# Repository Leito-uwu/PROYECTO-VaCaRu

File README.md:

**PROTOTIPO DE SISTEMA DE CLASIFICACIÓN DE BOTELLAS DE VIDRIO AUTOMATIZADO POR COLOR**

**📝 Descripción del Proyecto**

Bienvenido a nuestro sistema de clasificación de botellas automatizado. Este proyecto está diseñado para optimizar y agilizar el proceso de separación de botellas según sus características, para esto estamos utilizando tecnología de electronica, mecánica y automatización.

Con este sistema, buscamos mejorar la eficiencia en la gestión de residuos, reducir costos operativos y promover prácticas más sostenibles en el reciclaje de envases. Nuestra solución integra sensores, procesamiento de diferenciacion de colores y algoritmos de clasificación para lograr una identificación rápida y precisa de los materiales.

¡Explora el repositorio y conoce más sobre cómo funciona este innovador sistema!

**🎯 Características Principales**

- 🔍 Clasificación Inteligente: Utiliza un sensor para identificar las caracteristicas de la botella.
- ⚡ Automatización Total: El sistema funciona de manera autónoma, reduciendo la necesidad de intervención humana.
- 🔄 Eficiencia en Procesamiento: Alta velocidad de detección y clasificación para optimizar la gestión de residuos.
- 🤖 Integración con Sensores: Emplea sensores para detectar el material y color de la botella
- 🌱 Enfoque en Sostenibilidad: Contribuye a la mejora del reciclaje y la reducción del impacto ambiental.
- 🛠️ Flexibilidad y Escalabilidad: Puede adaptarse a diferentes entornos y tipos de botellas.

**⚙️ Instalación y Configuración**

Reconfirgurable y programable, en el sentido que se puede tener acceso al codigo por ser un prototipo, y tomando en cuenta su configuracion de los sensores y actuadores. 

**🚀 Cómo Usarlo**
    Guía sobre la Funcionalidad:
    1) Colocar la botella en el comienzo de la cinta transportadora.
    2) Mediante el tablero de control, iniciar el proceso por la botonera.
    3) Detección del sensor de color e infrarrojo.
    4) Una vez detectado el brazo procede a la sujetación de la botella segun su color.
    5) Clasifica la botella en su respectivo deposito.
**🔎 Tecnologías Utilizadas**
ACTUADORES: 1 Mator Paso a Paso
            5 Servomotores
            1 Sensor FC-51
            1 Sensor TCS3200
            1 Pantalla LCD con I2C
            2 Pulsadores
            1 Driver ULN2003    
**👥 Contribución**
Autores: Alberto Ruiz
         Ramiro Caucota
         Leonardo Vargas

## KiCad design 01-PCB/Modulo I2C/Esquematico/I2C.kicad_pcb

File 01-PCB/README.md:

**PCB 👨‍💻**

Este apartado incluye los archivos necesarios para la fabricación y ensamblaje de la PCB del proyecto, como diseños en formato Gerber, esquemáticos, lista de materiales, archivos CAD y guías de ensamblaje de PCBs. Su objetivo es proporcionar toda la documentación requerida para replicar, modificar o mejorar el diseño original, asegurando una correcta integración del hardware con el sistema.

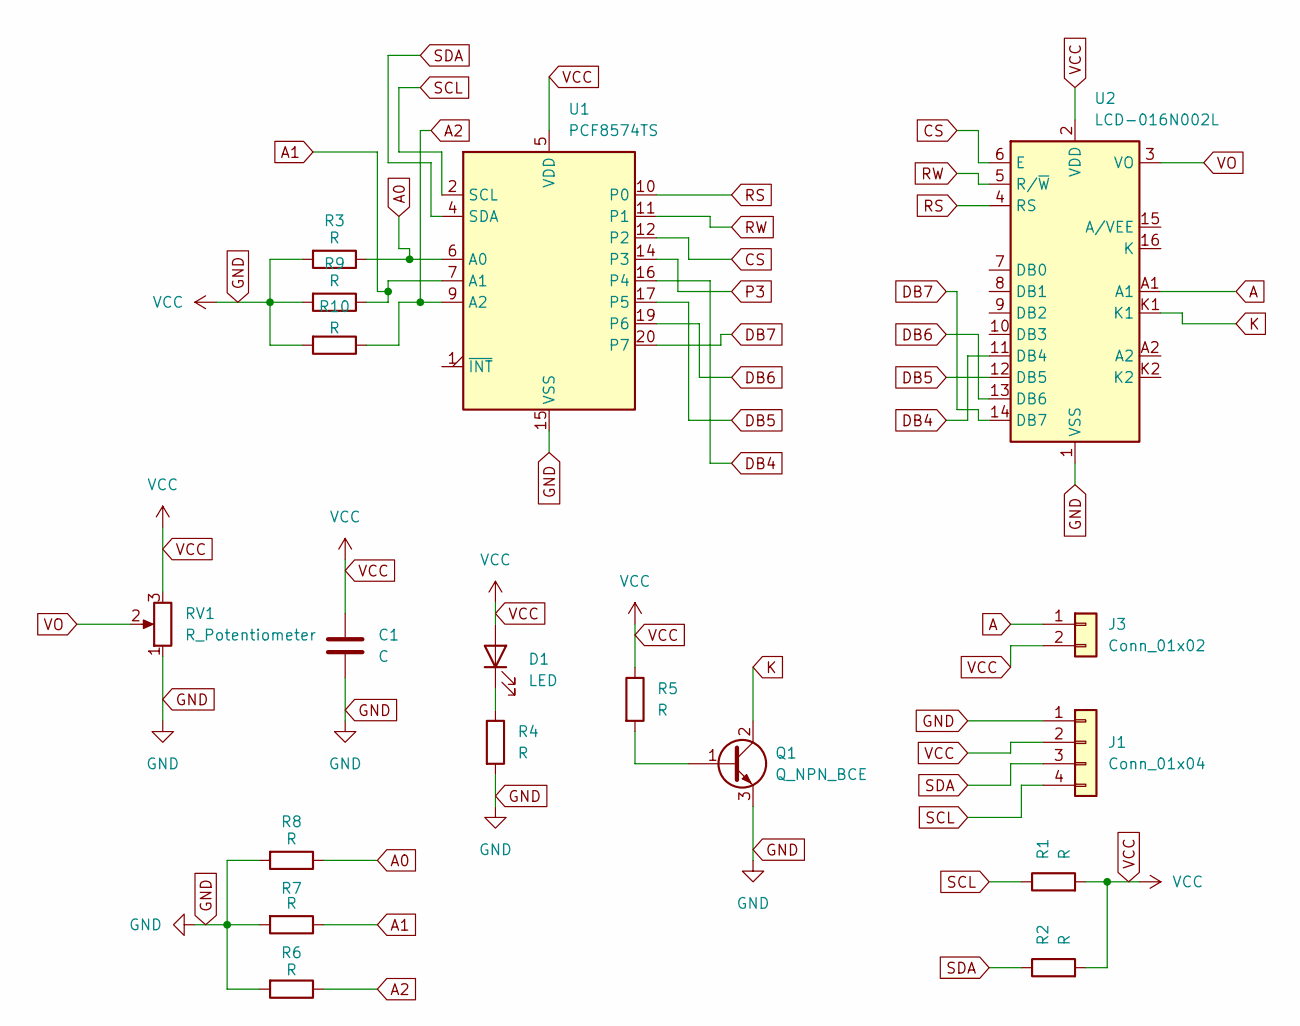
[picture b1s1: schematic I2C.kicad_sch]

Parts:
C1: C; C_0402_1005Metric
D1: LED; LED_D5.0mm_Horizontal_O1.27mm_Z3.0mm
J1: Conn_01x04; PhoenixContact_GMSTBA_2,5_4-G-7,62_1x04_P7.62mm_Horizontal
J3: Conn_01x02; PhoenixContact_GMSTBA_2,5_2-G_1x02_P7.50mm_Horizontal
Q1: Q_NPN_BCE; TO-92
R1, R2, R3, R4, R5, R6, R7, R8, R9, R10: R; R_0402_1005Metric
RV1: R_Potentiometer; Potentiometer_Bourns_3339H_Vertical
U1: PCF8574TS; SSOP-20_4.4x6.5mm_P0.65mm
U2: LCD-016N002L

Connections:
A: J3.1, U2.A1
A0: R3.1, R8.1, U1.6 (A0)
A1: R7.1, R9.1, U1.7 (A1)
A2: R6.1, R10.1, U1.9 (A2)
CS: U1.12 (P2), U2.6 (E)
DB4: U1.16 (P4), U2.11 (DB4)
DB5: U1.17 (P5), U2.12 (DB5)
DB6: U1.19 (P6), U2.13 (DB6)
DB7: U1.20 (P7), U2.14 (DB7)
GND: C1.1, C1.2, D1.2 (A), J1.1, J1.2, J3.2, Q1.3 (E), R1.2, R2.2, R3.2, R4.2, R5.1, R6.2, R7.2, R8.2, R9.2, R10.2, RV1.1, RV1.3, U1.5 (VDD), U1.15 (VSS), U2.1 (VSS), U2.2 (VDD)
K: Q1.2 (C), U2.K1
unnamed: D1.1 (K), R4.1
unnamed: Q1.1 (B), R5.2
P3: U1.14 (P3)
RS: U1.10 (P0), U2.4 (RS)
RW: U1.11 (P1), U2.5 (R/~W)
SCL: J1.4, R1.1, U1.2 (SCL)
SDA: J1.3, R2.1, U1.4 (SDA)
VO: RV1.2, U2.3 (VO)

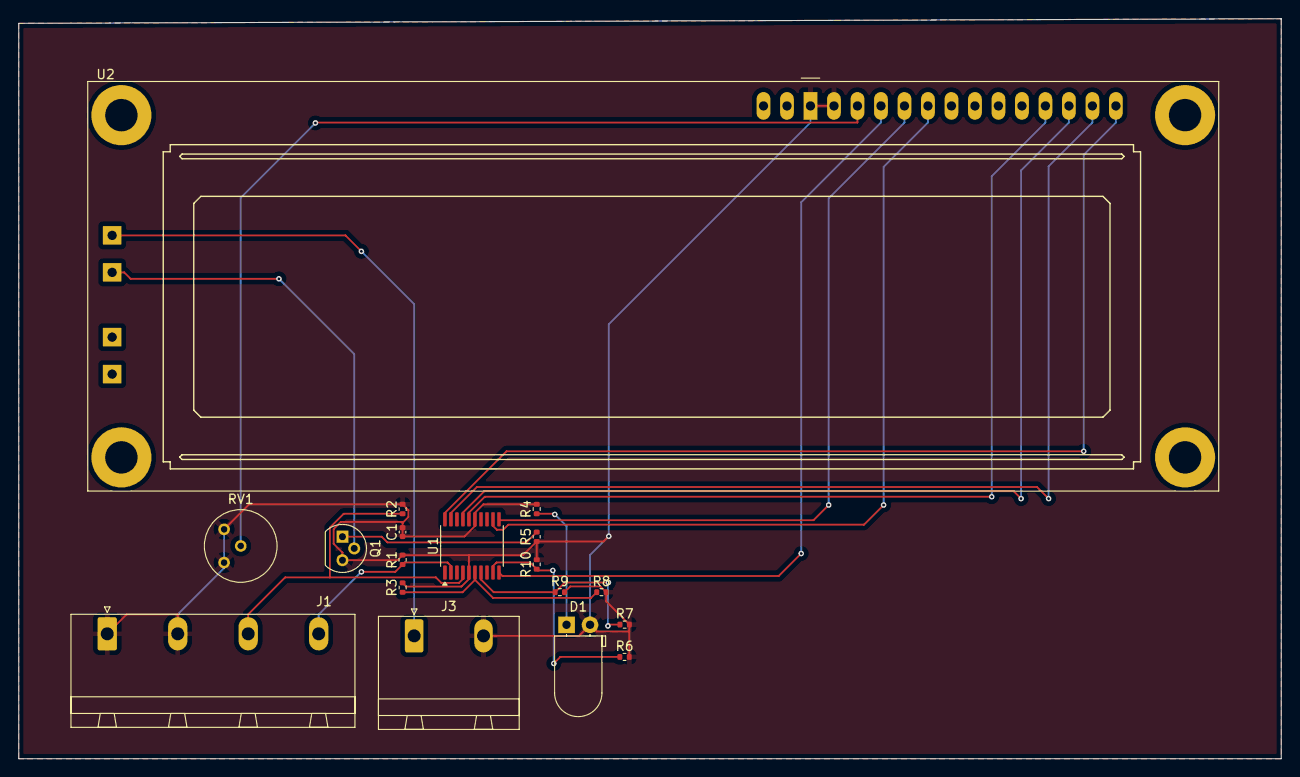
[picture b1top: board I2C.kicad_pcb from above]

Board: 2 copper layers, 136.5 x 80.0 mm, 18 parts (0 on the bottom side), 18 nets.

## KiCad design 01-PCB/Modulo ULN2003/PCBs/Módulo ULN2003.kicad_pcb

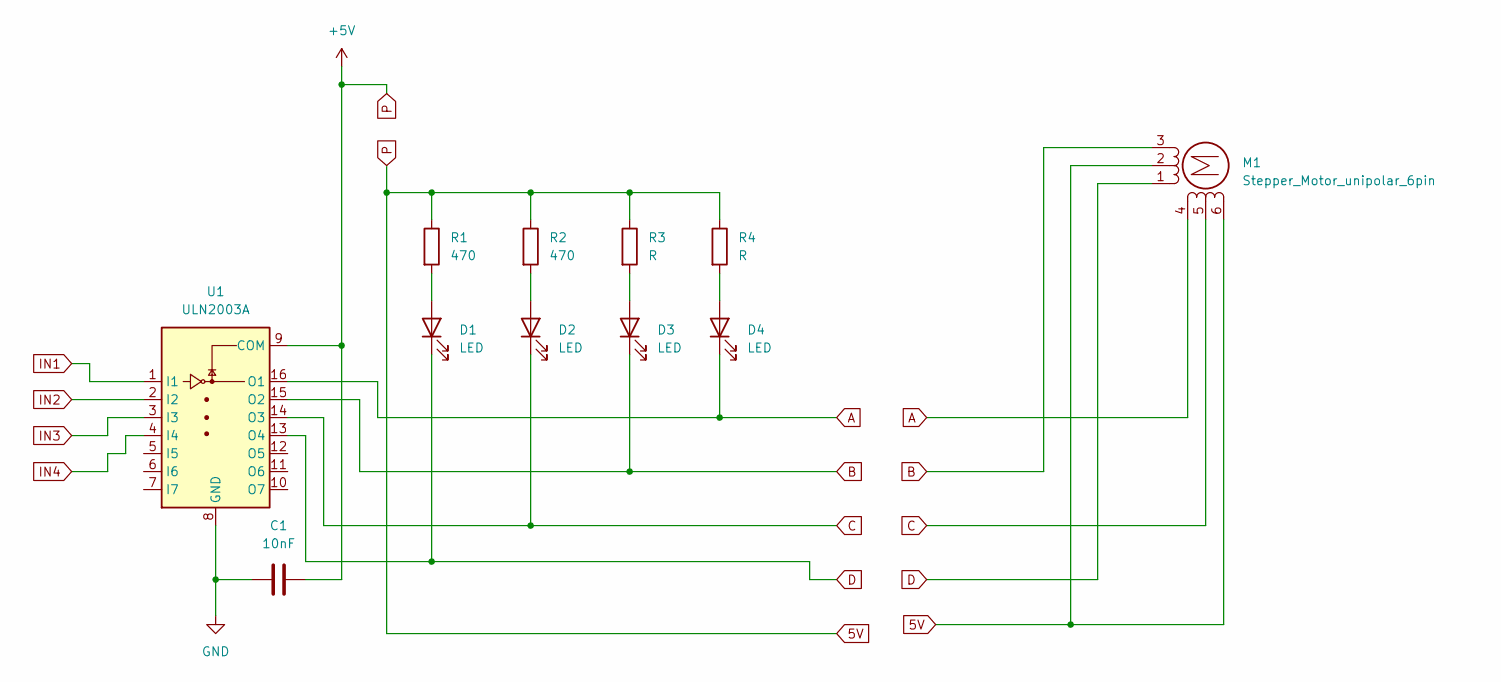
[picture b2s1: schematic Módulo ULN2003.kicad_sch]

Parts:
C1: 10nF; C_0402_1005Metric
D1, D2, D3, D4: LED; LED_D3.0mm
M1: Stepper_Motor_unipolar_6pin; PinSocket_1x06_P1.00mm_Vertical
R1, R2: 470; R_0402_1005Metric
R3, R4: R; R_0402_1005Metric
U1: ULN2003A; DIP-16_W7.62mm

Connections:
5V: C1.2, M1.2, M1.6, R1.1, R2.1, R3.1, R4.1, U1.9 (COM)
A: D4.1 (K), M1.4, U1.16 (O1)
B: D3.1 (K), M1.3 (-), U1.15 (O2)
C: D2.1 (K), M1.5, U1.14 (O3)
D: D1.1 (K), M1.1, U1.13 (O4)
GND: C1.1, U1.8 (GND)
IN1: U1.1 (I1)
IN2: U1.2 (I2)
IN3: U1.3 (I3)
IN4: U1.4 (I4)
unnamed: D1.2 (A), R1.2
unnamed: D2.2 (A), R2.2
unnamed: D3.2 (A), R3.2
unnamed: D4.2 (A), R4.2

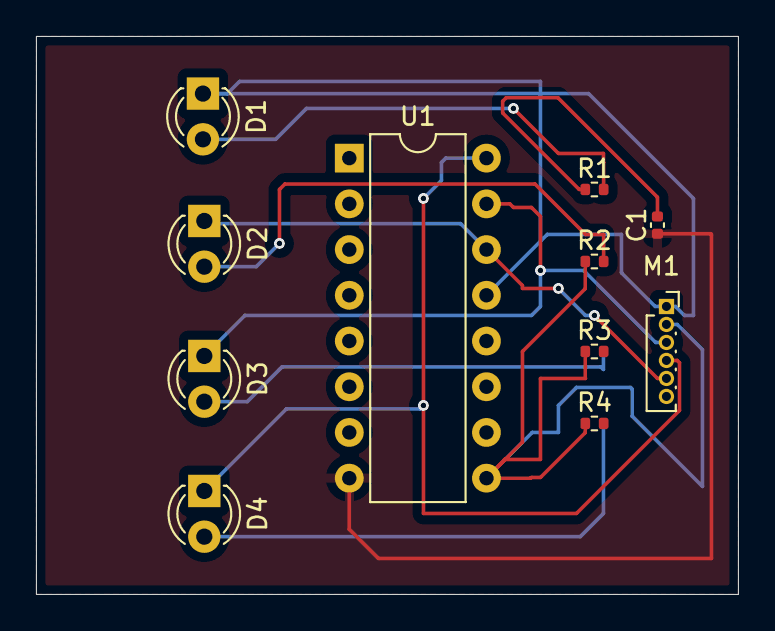
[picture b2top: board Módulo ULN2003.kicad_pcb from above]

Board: 2 copper layers, 39.0 x 31.0 mm, 11 parts (0 on the bottom side), 10 nets.

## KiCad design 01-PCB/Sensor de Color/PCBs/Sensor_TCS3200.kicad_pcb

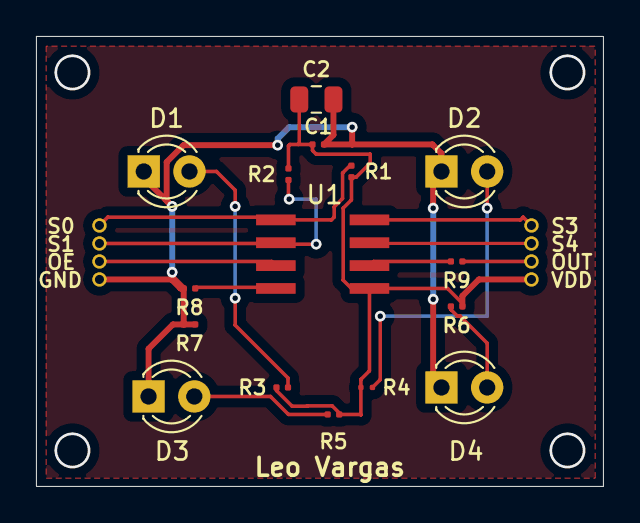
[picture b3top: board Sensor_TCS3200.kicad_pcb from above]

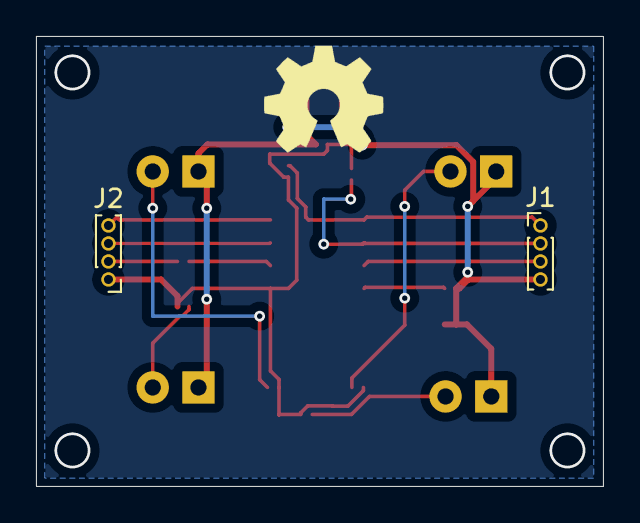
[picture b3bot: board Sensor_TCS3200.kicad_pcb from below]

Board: 2 copper layers, 31.5 x 25.0 mm, 18 parts (2 on the bottom side), 14 nets.

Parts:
C1: 100nF; C_0201_0603Metric
C2: 10uF; C_0805_2012Metric
D1, D2, D3, D4: D; LED_D3.0mm_Clear
J1, J2: Conn_01x04_Pin; PinHeader_1x04_P1.00mm_Vertical
R1, R2: 10k; R_0201_0603Metric
R3, R4, R5, R6: 330; R_0201_0603Metric
R7, R8: 0; R_0201_0603Metric
R9: 1k; R_0201_0603Metric
U1: TCS3200D; SOIC8

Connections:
GND: C1.2, C2.2, D1.1 (K), D2.1 (K), D3.1 (K), D4.1 (K), J1.4, R7.1, R7.2, R8.2
unnamed: D1.2 (A), R3.2
unnamed: D2.2 (A), R4.2
unnamed: D3.2 (A), R5.2
unnamed: D4.2 (A), R6.2
unnamed: J1.1, R1.2, U1.1 (S0)
unnamed: J1.2, R2.2, U1.2 (S1)
unnamed: J1.3, U1.3 (OE)
unnamed: C1.1, C2.1, J2.1, R1.1, R2.1, R3.1, R4.1, R5.1, R6.1, U1.5 (VDD)
unnamed: J2.2, R9.1
unnamed: J2.3, U1.7 (S2)
unnamed: J2.4, U1.8 (S3)
unnamed: R8.1, U1.4 (GND)
unnamed: R9.2, U1.6 (OUT)

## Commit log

2025-06-01 inicio
2025-06-01 codigo
2025-06-01 maestro v1
2025-06-01 maestro v1.0
2025-06-01 cambios 1
2025-06-02 Readme1(Carlos)
2025-06-02 Cambio_1
2025-06-02 Cambio_2
2025-06-03 Actualizacion del README.md principal
2025-06-03 Acualizacion del la documentacion
2025-06-03 intento-1
2025-06-03 Documentos S.Color
2025-06-03 Acualizacion en general
2025-06-03 Actualizacion General
2025-06-03 Leo Color
2025-06-03 Segunda Version de Codigo
2025-06-03 Nuevo Cambio
2025-06-03 Documentacion-L
2025-06-03 Pruevas Brazo
2025-06-04 Cambio de Alberto!!!
2025-06-06 Nuevo Maestro
2025-06-06 Mejorado
2025-06-07 Pruevas Varias y ESCLAVO I2C
2025-06-08 Maestro con I2C
2025-06-08 Planos y modelos de cinta
2025-06-09 Maestro Filtro!!!
2025-06-09 codigo pulido
2025-06-12 Modificaciones
2025-06-12 Cambio De Esclavo Alberto!!!
2025-06-12 Maestro_Modularizado
2025-06-12 Cambios!!
